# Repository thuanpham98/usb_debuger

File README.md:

# usb_debuger

## Hardware

### Schematics

### PCB Layout

#### Parameter

#### Top side

#### Back side

### 3D

#### Top side

#### Back side

### Gerber

Version 0.0

- [Gerber V0.0](./assets/demo/gerber.rar)

### Remark

This project was in development phase - we will remove this remark after release

# License

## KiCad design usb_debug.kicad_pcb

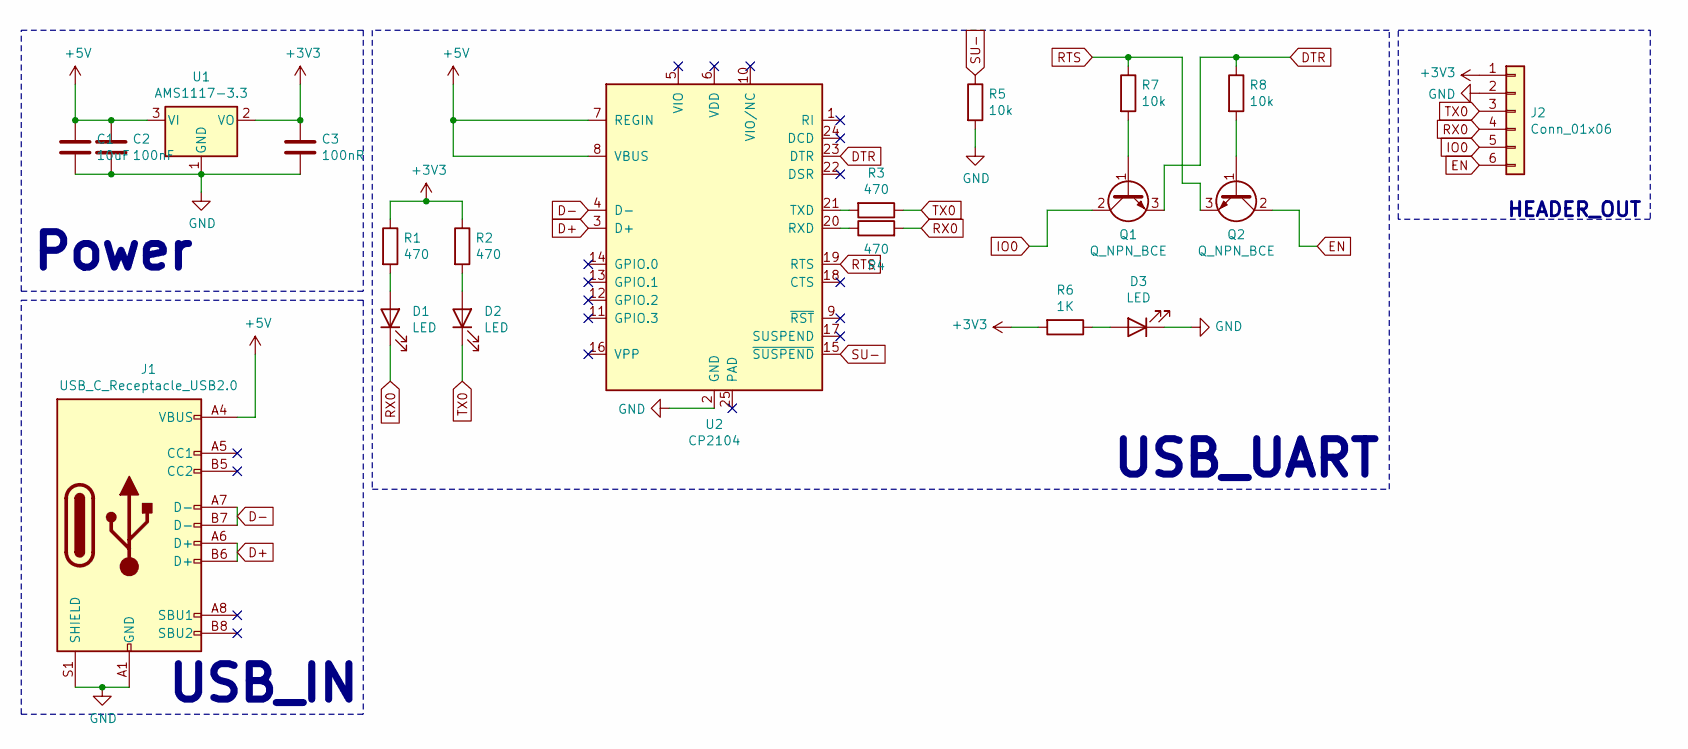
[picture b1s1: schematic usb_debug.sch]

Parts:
C1: 10uF; C_1210_3225Metric
C2: 100nF; C_0603_1608Metric
C3: 100nR; C_0603_1608Metric
D1, D2, D3: LED; D_0603_1608Metric
J1: USB_C_Receptacle_USB2.0; USB_C_Receptacle_HRO_TYPE-C-31-M-12
J2: Conn_01x06; PinHeader_1x06_P2.54mm_Vertical
Q1, Q2: Q_NPN_BCE; SOT-23
R1, R2, R3, R4: 470; R_0603_1608Metric
R5, R7, R8: 10k; R_0603_1608Metric
R6: 1K; R_0603_1608Metric
U1: AMS1117-3.3; SOT-223-3_TabPin2
U2: CP2104; QFN-24-1EP_4x4mm_P0.5mm_EP2.6x2.6mm

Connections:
+3V3: C3.1, J2.1, R1.1, R2.1, R6.2, U1.2 (VO)
+5V: C1.2, C2.1, J1.A4 (VBUS), J1.A9 (VBUS), J1.B4 (VBUS), J1.B9 (VBUS), U1.3 (VI), U2.7 (REGIN), U2.8 (VBUS)
D+: J1.A6 (D+), J1.B6 (D+), U2.3 (D+)
D-: J1.A7 (D-), J1.B7 (D-), U2.4 (D-)
DTR: Q1.3 (E), R8.1, U2.23 (DTR)
EN: J2.6, Q2.2 (C)
GND: C1.1, C2.2, C3.2, D3.1 (K), J1.A1 (GND), J1.A12 (GND), J1.B1 (GND), J1.B12 (GND), J1.S1 (SHIELD), J2.2, R5.2, U1.1 (GND), U2.2 (GND)
IO0: J2.5, Q1.2 (C)
unnamed: D1.2 (A), R1.2
unnamed: D2.2 (A), R2.2
unnamed: D3.2 (A), R6.1
unnamed: Q1.1 (B), R7.2
unnamed: Q2.1 (B), R8.2
unnamed: R3.2, U2.21 (TXD)
unnamed: R4.1, U2.20 (RXD)
RTS: Q2.3 (E), R7.1, U2.19 (RTS)
RX0: D1.1 (K), J2.4, R4.2
SU-: R5.1, U2.15 (~SUSPEND)
TX0: D2.1 (K), J2.3, R3.1

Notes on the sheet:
USB_UART
Power
USB_IN
HEADER_OUT

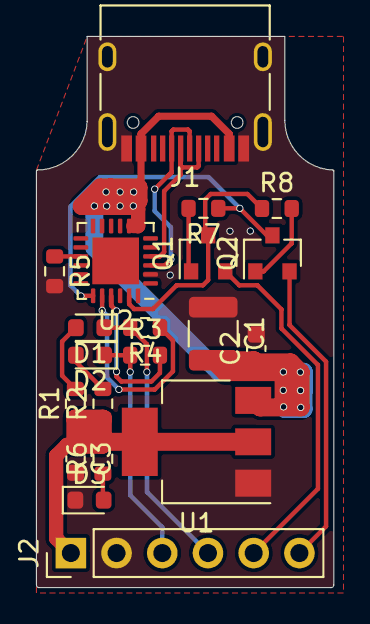
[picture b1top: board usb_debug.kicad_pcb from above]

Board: 2 copper layers, 16.5 x 30.6 mm, 20 parts (0 on the bottom side), 19 nets.

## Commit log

2021-05-04 init
2021-05-04 add gitignore
